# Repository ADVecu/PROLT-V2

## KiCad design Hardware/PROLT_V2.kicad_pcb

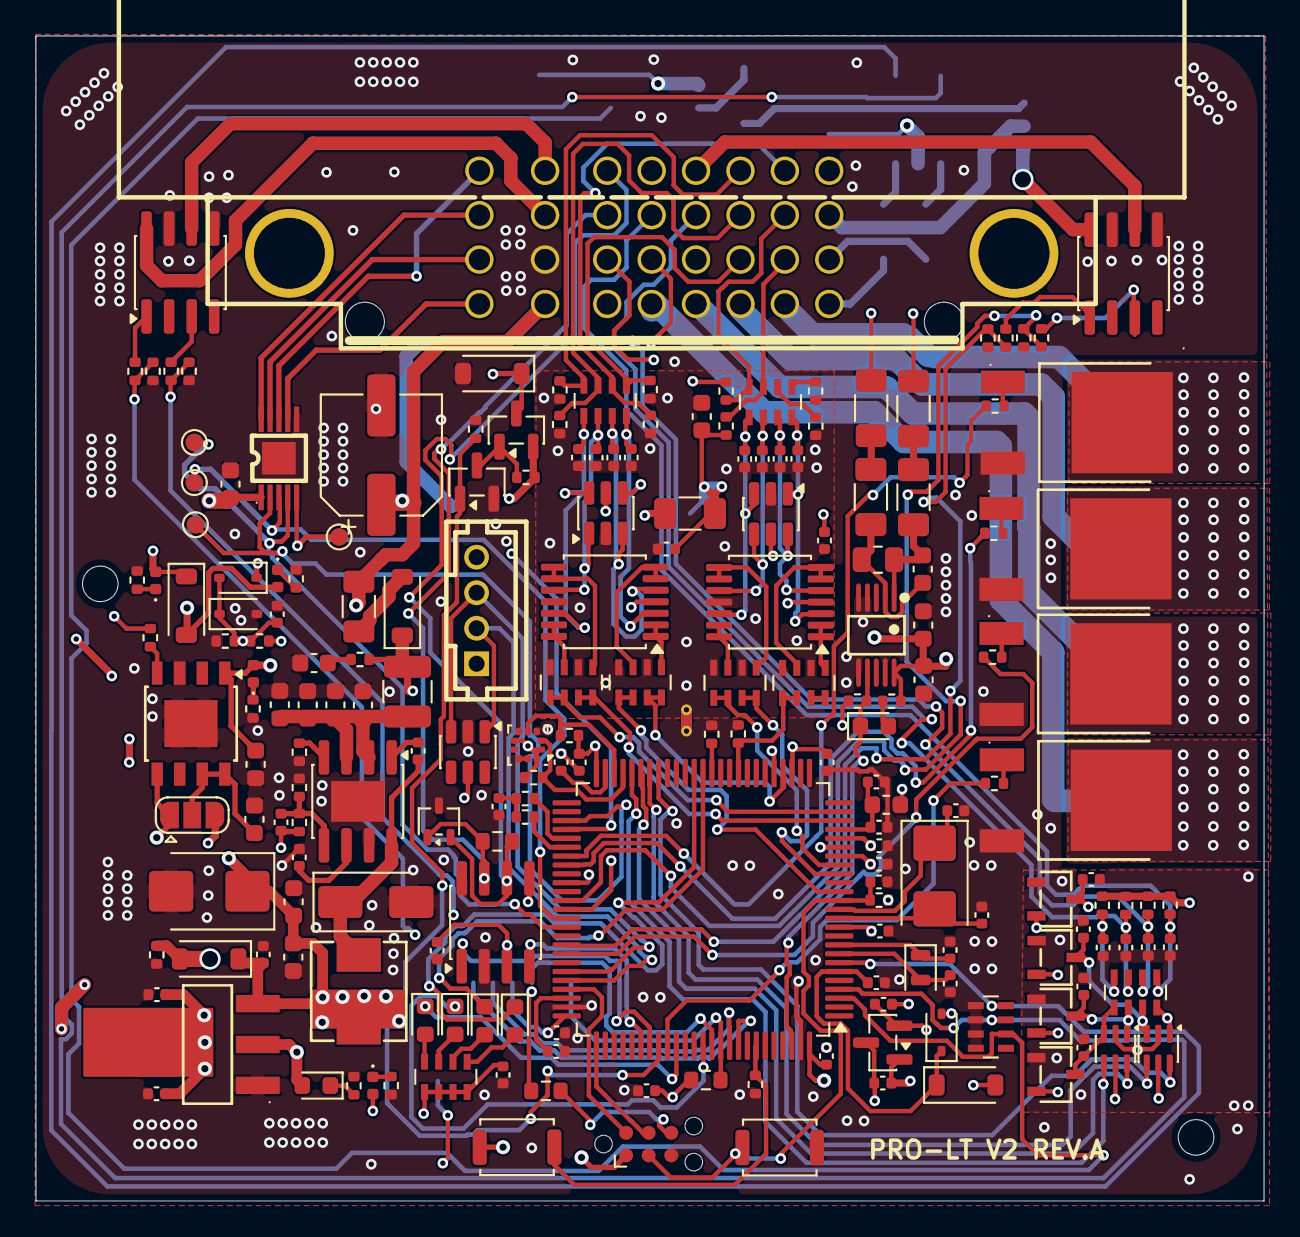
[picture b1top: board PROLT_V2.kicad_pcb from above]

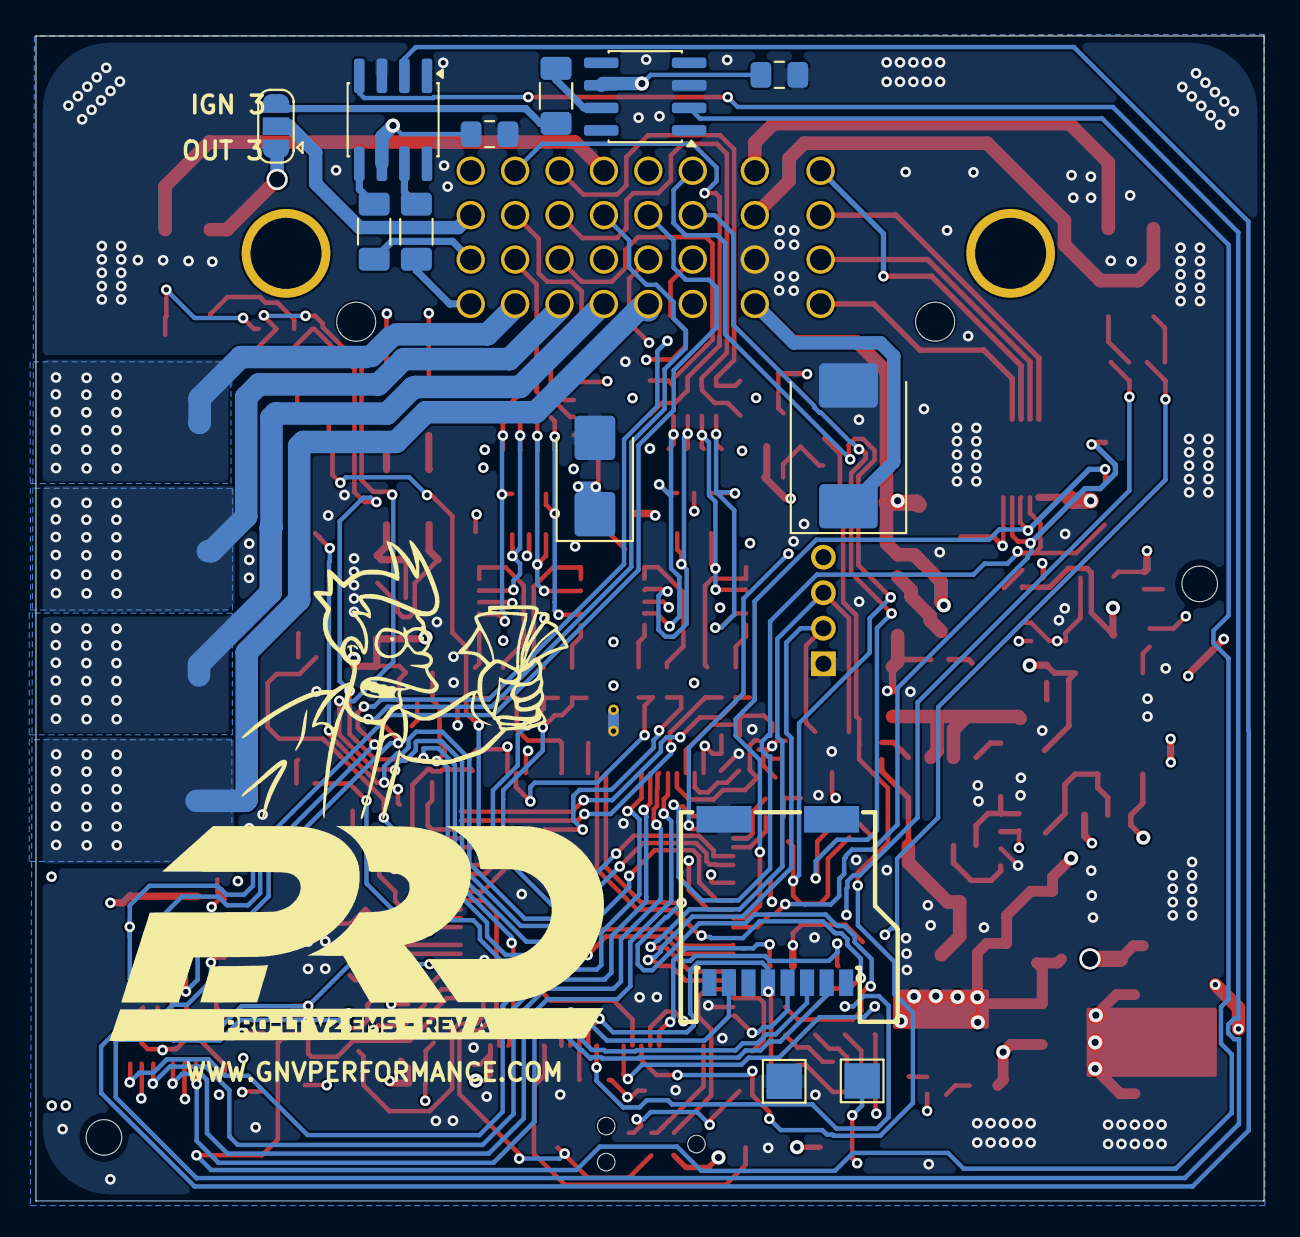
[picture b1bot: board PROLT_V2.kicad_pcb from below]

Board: 4 copper layers, 69.1 x 65.6 mm, 209 parts (13 on the bottom side), 162 nets.

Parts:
C201, C202: 18pF; C_0402_1005Metric
C203: 1uF; C_0402_1005Metric
C204, C208, C209, C210, C211, C212, C213, C214, C221, C223, C224, C226, C309, C312, C410, C411: 100nF; C_0402_1005Metric
C205, C206: 2.2uF; C_0402_1005Metric
C207, C217, C218, C219, C220, C222, C225: 4.7pF; C_0402_1005Metric
C215, C216: 12pF; C_0402_1005Metric
C301: 4.7u; C_0603_1608Metric
C302, C307: 1u; C_0603_1608Metric
C303, C304, C305, C306: 10uF; C_0603_1608Metric
C308, C402, C403, C404, C405, C406, C407, C408, C409: 10nF; C_0402_1005Metric
C310: 220pF; C_0402_1005Metric
C311, C313: 10u; C_0603_1608Metric
C401, C803, C901: 100n; C_0603_1608Metric
C501, C502, C503, C504, C505, C506, C507, C508: 1n; C_0402_1005Metric
C701, C702: 100nF; C_0805_2012Metric_Pad1.18x1.45mm_HandSolder
C801: 1n; C_0603_1608Metric
C802: 22uF; C_0603_1608Metric
C902: 47uF; CP_Elec_6.3x5.4
Card201: TF-004; TF-SMD_TF-004
D201, D202, D303, D307: B5819W; D_SOD-123
D203, D206, D801: GREEN; LED_0603_1608Metric
D204: PESD1CAN; SOT-323_SC-70
D205: RED; LED_0603_1608Metric
D207: BLUE; LED_0603_1608Metric
D208: YELLOW; LED_0603_1608Metric
D301: SM15T33CA; D_SMC
D302, D311, D312: 1N4148WS; D_SOD-323
D304, D305, D308, D310: BLUE; LED_0402_1005Metric
D306: SS34; D_SMA
D309, D401: P6SMB6.8CA; D_SMB
D501, D502, D503, D504: BAT54S,215; SOT-23-3_L3.0-W1.7-P0.95-LS2.9-BR
D601: 1N4148W; D_SOD-123
F301: 500mA; Fuse_1206_3216Metric
F401: SMD1206B035TF; Fuse_1206_3216Metric
FB201: FerriteBead; L_0603_1608Metric
J201: TC2030-NL; Tag-Connect_TC2030-IDC-NL_2x03_P1.27mm_Vertical
JP101: OUT3 SEL; SolderJumper-3_P1.3mm_Open_RoundedPad1.0x1.5mm
JP301: PwSupply; SolderJumper-3_P1.3mm_Open_RoundedPad1.0x1.5mm
L301: 2.2u; L_1210_3225Metric
L302: MWSA0503S-100MT; IND-SMD_L5.4-W5.2
NT401: StarPoint GND; NetTie-2_THT_Pad0.3mm
Q601: AO3407A; SOT-23
Q602: AO3400A; SOT-23
R201, R202: 510; R_0402_1005Metric
R203, R205, R206, R210, R211, R213, R303, R311, R601, R602, R603, R604, R605, R606, R611, R612, R806, R807: 10k; R_0402_1005Metric
R204: 100; R_0603_1608Metric
R207, R208: 2.2k; R_0402_1005Metric
R209: 120; R_0603_1608Metric
R212: 33k; R_0603_1608Metric
R301, R305, R308, R310: 33k; R_0402_1005Metric
R302: 1; R_0402_1005Metric
R304: 23.7k; R_0402_1005Metric
R306: 12k; R_0402_1005Metric
R307: 68k; R_0402_1005Metric
R309: 6.8k; R_0402_1005Metric
R401, R402, R403, R404, R406, R408: 680k; R_0402_1005Metric
R405, R407, R501, R502, R503, R504, R607, R608, R609, R610, R613, R614: 4.7k; R_0402_1005Metric
R701, R702, R703: 100; R_1206_3216Metric_Pad1.30x1.75mm_HandSolder
R801, R802, R803, R804: 4.7k; R_1206_3216Metric_Pad1.30x1.75mm_HandSolder
R805: DNP; R_0805_2012Metric
RN201: R_Pack04; R_Array_Concave_4x0603
RN401, RN402, RN403, RN404, RN405, RN406: 4.7k; R_Array_Concave_4x0603
RN501, RN701: 10k; R_Array_Concave_4x0603
SW201: Boot; SW_Push_SPST_NO_Alps_SKRK
SW202: Reset; SW_Push_SPST_NO_Alps_SKRK
TP301: BATT+; TestPoint_Pad_2.0x2.0mm
TP302: GND; TestPoint_Pad_2.0x2.0mm
TP901: STP1; TestPoint_Pad_D1.0mm
TP902: STP2; TestPoint_Pad_D1.0mm
TP903: STP3; TestPoint_Pad_D1.0mm
TP904: STP4; TestPoint_Pad_D1.0mm
U101: 643340100; CONN-TH_643340100
U201: STM32F407VGTx; LQFP-100_14x14mm_P0.5mm
U202: LPS22HB; ST_HLGA-10_2x2mm_P0.5mm_LayoutBorder3x2y
U203, U401, U402: SRV05-4; SOT-23-6
U204: B4B-PH-K-K; CONN-TH_B4B-PH-K-S-LF-SN
U205: LDL1117S33R; SOT-223-4_L6.5-W3.5-P2.30-LS7.0-BR
U206: TJA1051T-3; SOIC-8_3.9x4.9mm_P1.27mm
U207: REF3033; SOT-23
U301: TLS115; Infineon_PG-DSO-8-43
U302: LMR14020; SOIC-8-1EP_3.9x4.9mm_P1.27mm_EP2.29x3mm
U403, U404: MCP6004T-I-ST; TSSOP-14_4.4x5mm_P0.65mm
U501, U502: 74LVC2G17; SOT-363_SC-70-6
U601, U602, U605, U606: BTS3046SDRATMA1; PG-TO252-3_L6.5-W6.2-P4.57-LS10.0-BR-CW-1
U603, U604: VNLD5160TR-E; SOIC-8_3.9x4.9mm_P1.27mm
U701, U702: MIC4427; SOIC-8_3.9x4.9mm_P1.27mm
U801: MAX9924UAUB+; MSOP-10_L3.0-W3.0-P0.50-LS5.0-BL
U901: DRV8421ADGQR; HVSSOP-10_L3.0-W3.0-P0.50-LS4.9-BL-EP
Y201: 8MHz 20pF; Crystal_SMD_5032-2Pin_5.0x3.2mm
Y202: 32.768 kHz; Crystal_SMD_2012-2Pin_2.0x1.2mm

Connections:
+5V: C217.2, C220.2, C226.2, C310.1, C311.1, C313.1, C701.1, C702.1, C802.1, C803.1, D202.1 (K), D309.1 (K), D310.2 (A), F401.1, JP301.1 (A), L302.2, R307.2, R807.1, U205.3 (VIN), U206.3 (VCC), U207.1 (IN), U301.5 (ADJ), U701.6 (V_{S}), U702.6 (V_{S}), U801.10 (VCC)
/5VA: C401.1, C410.2, C411.2, D401.1 (K), D501.2 (K), D502.2 (K), D503.2 (K), D504.2 (K), F401.2, R405.1, R407.1, R501.1, R502.1, R503.1, R504.1, U401.5 (VP), U402.5 (VP), U403.4 (V+), U404.4 (V+), U501.5 (VCC), U502.5 (VCC)
/5V_SENSOR: C307.1, D305.2 (A), U101.F1, U301.1 (OUT)
/12V_KEY: C901.1, C902.1, D301.1 (A1), D307.2 (A), D308.2 (A), F301.1, R308.2, U101.G1, U901.1 (VM)
/12V_PROT: D303.1 (K), D304.2 (A), D307.1 (K), JP301.3 (B), L301.1, Q601.2 (S), R302.1, R613.1
/A+: U101.H3, U901.10 (OUT1)
/A-: U101.H2, U901.9 (OUT2)
/Analaog/IN5: R401.1, RN401.1 (R1.1)
/Analaog/IN6: R403.1, RN401.2 (R2.1)
/Analaog/OUT1: RN405.7 (R2.2), RN405.8 (R1.2), U201.29 (PA4)
/Analaog/OUT2: RN405.5 (R4.2), RN405.6 (R3.2), U201.15 (PC0)
/Analaog/OUT3: RN406.7 (R2.2), RN406.8 (R1.2), U201.23 (PA0)
/Analaog/OUT4: RN406.5 (R4.2), RN406.6 (R3.2), U201.24 (PA1)
/Analaog/OUT5: RN403.7 (R2.2), RN403.8 (R1.2)
/Analaog/OUT6: R205.2, RN403.5 (R4.2), RN403.6 (R3.2), U201.34 (PC5)
/Analaog/OUT_AT1: RN404.7 (R2.2), RN404.8 (R1.2), U201.17 (PC2)
/Analaog/OUT_AT2: RN404.5 (R4.2), RN404.6 (R3.2), U201.18 (PC3)
/B+: U101.H4, U901.8 (OUT3)
/B-: U101.H1, U901.7 (OUT4)
/CAN_H: D204.1 (A1), R209.1, U101.F3, U206.7 (CANH)
/CAN_L: D204.2 (A2), R209.2, U101.F4, U206.6 (CANL)
/Digital/HALL_IN_4: C502.1, R502.2, RN501.4 (R4.1)
/Digital/HALL_OUT_1: U201.43 (PE12), U501.6
/Digital/HALL_OUT_2: U201.44 (PE13), U501.4
/Digital/HALL_OUT_3: U201.45 (PE14), U502.6
/Digital/HALL_OUT_4: U201.46 (PE15), U502.4
/IGN1_OUT: R701.2, U101.A1
/IGN2_OUT: R702.2, U101.A2
/IGN3_OUT: JP101.3 (B), R703.2
/INJ1_OUT: U101.E1, U601.2 (DRAIN)
/INJ2_OUT: U101.D1, U602.2 (DRAIN)
/INJ3_OUT: U101.C1, U605.2 (DRAIN)
/INJ4_OUT: U101.B1, U606.2 (DRAIN)
/IN_AUX1: R406.1, RN402.3 (R3.1), U101.C3
/IN_AUX2: R408.1, RN402.4 (R4.1), U101.C4
/IN_CLT: R407.2, RN401.4 (R4.1), U101.B3
/IN_CMP: C503.1, R503.2, RN501.1 (R1.1), U101.E3
/IN_D1: C504.1, R504.2, RN501.2 (R2.1), U101.D2
/IN_D2: C501.1, R501.2, RN501.3 (R3.1), U101.D3
/IN_IAT: R405.2, RN401.3 (R3.1), U101.B2
/IN_MAP: R404.1, RN402.2 (R2.1), U101.B4
/IN_TPS: R402.1, RN402.1 (R1.1), U101.C2
/Ignition/IN_IGN1: RN701.8 (R1.2), U201.7 (PC13), U701.2 (INA)
/Ignition/IN_IGN2: RN701.7 (R2.2), U201.4 (PE5), U701.4 (INB)
/Ignition/IN_IGN3: RN701.6 (R3.2), U201.3 (PE4), U702.2 (INA)
/MCU/BOOT: R211.1, SW201.2, U201.94 (BOOT0)
/MCU/I2C_SCL: R208.2, U201.47 (PB10), U202.2 (SCL)
/MCU/I2C_SDA: R207.2, U201.48 (PB11), U202.4 (SDA)
/MCU/IN_AUX2_(PC4/PE9): U201.33 (PC4), U201.40 (PE9)
/MCU/IN_VIGN_(PA5): C312.2, D311.2 (A), D312.1 (K), R308.1, R309.2, U201.30 (PA5)
/MCU/LED1: D205.1 (K), U201.85 (PD4)
/MCU/LED2: D206.1 (K), U201.88 (PD7)
/MCU/LED3: D207.1 (K), U201.38 (PE7)
/MCU/LED4: D208.1 (K), U201.39 (PE8)
/MCU/OUT_INJ1_(PD3): R601.1, U201.84 (PD3)
/MCU/OUT_INJ2_(PA9): R602.1, U201.68 (PA9)
/MCU/OUT_INJ3_(PD11): R611.1, U201.58 (PD11)
/MCU/OUT_INJ4_(PD10): R612.1, U201.57 (PD10)
/MCU/OUT_INJ5_(PD2): Q602.1 (G), R614.1, U201.83 (PD2)
/MCU/OUT_INJ6_(PA8): R604.2, R609.2, U201.67 (PA8)
/MCU/OUT_INJ7_(PD15): R606.2, R610.2, U201.62 (PD15)
/MCU/OUT_PWM1_(PD13): R603.2, R607.2, U201.60 (PD13)
/MCU/OUT_PWM2_(PC6): R605.2, R608.2, U201.63 (PC6)
/MCU/RESET: C223.2, J201.3 (~RESET), R213.2, SW202.2, U201.14 (NRST)
/MCU/RXDCAN: U201.81 (PD0), U206.4 (RXD)
/MCU/SD_CS: Card201.2 (CD/DAT3), U201.92 (PB6)
/MCU/SD_MISO: Card201.7 (DAT0), R212.1, U201.90 (PB4)
/MCU/SD_MOSI: Card201.3 (CMD), U201.91 (PB5)
/MCU/SD_SCK: Card201.5 (CLK), R204.1, U201.89 (PB3)
/MCU/SWCLK: J201.4 (SWCLK), U201.76 (PA14)
/MCU/SWDIO: J201.2 (SWDIO), U201.72 (PA13)
/MCU/SWO: J201.6 (SWO), R204.2
/MCU/TXDCAN: U201.82 (PD1), U206.1 (TXD)
/MCU/UART8_TX_(PE1): D801.1 (K), R806.2, U201.98 (PE1), U801.7 (COUT)
/MCU/USBD+: U201.71 (PA12), U203.1 (IO1), U204.2
/MCU/USBD-: U201.70 (PA11), U203.3 (IO2), U204.3
/MCU/VBAT: C207.2, D201.1 (K), D302.1 (K), U201.6 (VBAT)
/MCU/VBUS: D202.2 (A), R206.1, U203.5 (VP), U204.4
/MCU/VDDA: C214.2, C225.2, FB201.2, U201.22 (VDDA)
/MCU/VREF: C204.2, C222.2, U201.21 (VREF+), U207.2 (OUT)
/OUT_1: U101.G3, U603.8 (D1)
/OUT_2: U101.G4, U603.6 (D2)
/OUT_3: JP101.1 (A), U604.8 (D1)
/OUT_4: U101.D4, U604.6 (D2)
/Power/5V_SENSOR_PG: R303.1, U301.4 (PG)
/Power/SensorTrackerPS: C302.1, JP301.2 (C), U301.7 (EN), U301.8 (IN)
/STEPPER_IN1: TP901.1 (1_1), U201.53 (PB14), U901.2 (IN1)
/STEPPER_IN2: TP902.1 (1_1), U201.64 (PC7), U901.3 (IN2)
/STEPPER_IN3: TP903.1 (1_1), U201.65 (PC8), U901.4 (IN3)
/STEPPER_IN4: TP904.1 (1_1), U201.54 (PB15), U901.5 (IN4)
/TACH: D601.1 (K), Q601.3 (D), U101.A4
/V33: C208.1, C209.1, C210.1, C211.1, C212.1, C213.1, C218.2, C219.2, C221.2, C224.2, Card201.4 (VDD), D201.2 (A), D203.2 (A), D311.1 (K), FB201.1, J201.1 (VCC), R207.1, R208.1, R212.2, R213.1, R303.2, R806.1, RN201.1 (R1.1), RN201.2 (R2.1), RN201.3 (R3.1), RN201.4 (R4.1), SW201.1, U201.11 (VDD), U201.19 (VDD), U201.28 (VDD), U201.50 (VDD), U201.75 (VDD), U201.100 (VDD), U202.1 (Vdd_IO), U202.6 (~CS), U202.10 (VDD), U205.2 (VOUT), U205.4 (VOUT), U206.5 (VIO)
/VR+: R801.1, U101.F2
/VR-: R802.1, U101.E2
GND: C201.1, C202.1, C203.2, C204.1, C205.1, C206.1, C207.1, C208.2, C209.2, C210.2, C211.2, C212.2, C213.2, C214.1, C215.1, C216.1, C217.1, C218.1, C219.1, C221.1, C223.1, C224.1, C225.1, C226.1, C301.2, C302.2, C303.2, C304.2, C305.2, C306.2, C307.2, C308.2, C311.2, C312.1, C313.2, C701.2, C702.2, C802.2, C803.2, C901.2, C902.2, Card201.6 (VSS), Card201.9 (GND), Card201.10 (GND), D204.3 (Com), D301.2 (A2), D306.2 (A), D309.2 (A), D312.2 (A), D401.2 (A), D601.2 (A), J201.5 (GND), NT401.2, Q602.2 (S), R203.2, R205.1, R206.2, R210.2, R211.2, R301.1, R304.2, R305.1, R306.2, R309.1, R310.1, R311.2, R603.1, R604.1, R605.1, R606.1, R614.2, RN701.1 (R1.1), RN701.2 (R2.1), RN701.3 (R3.1), RN701.4 (R4.1), SW202.1, TP302.1 (1_1), U101.G2, U201.10 (VSS), U201.27 (VSS), U201.74 (VSS), U201.99 (VSS), U202.3 (GND), U202.5 (SA0), U202.8 (GND), U202.9 (GND), U203.2 (VN), U204.1, U205.1 (GND), U206.2 (GND), U206.8 (S), U301.3 (GND), U301.9 (GND), U302.7 (GND), U302.9 (GND), U601.3 (SOURCE), U602.3 (SOURCE), U603.5 (S2), U603.7 (S1), U604.5 (S2), U604.7 (S1), U605.3 (SOURCE), U606.3 (SOURCE), U701.3 (GND), U702.3 (GND), U801.4 (BIAS), U801.5 (GND), U801.6 (ZERO_EN), U801.9 (INT_THRS), U901.6 (GND), U901.11 (GND)
GNDA: C220.1, C222.1, C401.2, C402.2, C403.2, C404.2, C405.2, C406.2, C407.2, C408.2, C409.2, C410.1, C411.1, C501.2, C502.2, C503.2, C504.2, C505.2, C506.2, C507.2, C508.2, D501.1 (A), D502.1 (A), D503.1 (A), D504.1 (A), NT401.1, R401.2, R402.2, R403.2, R404.2, R406.2, R408.2, RN403.2 (R2.1), RN403.4 (R4.1), RN404.2 (R2.1), RN404.4 (R4.1), RN405.2 (R2.1), RN405.4 (R4.1), RN406.2 (R2.1), RN406.4 (R4.1), U101.E4, U201.20 (VSSA), U207.3 (GND), U401.2 (VN), U402.2 (VN), U403.11 (V-), U404.11 (V-), U501.2 (GND), U502.2 (GND)
unnamed: C203.1, R201.1, R202.1
unnamed: C301.1, R302.2
unnamed: D203.1 (K), R210.1
unnamed: D205.2 (A), RN201.8 (R1.2)
unnamed: D206.2 (A), RN201.7 (R2.2)
unnamed: D207.2 (A), RN201.6 (R3.2)
unnamed: D208.2 (A), RN201.5 (R4.2)
unnamed: D302.2 (A), TP301.1 (1_1)
unnamed: D303.2 (A), F301.2
unnamed: D304.1 (K), R301.2
unnamed: D305.1 (K), R305.2
unnamed: C309.1, D306.1 (K), L302.1, U302.8 (SW)
unnamed: D308.1 (K), R310.2
unnamed: D310.1 (K), R311.1
unnamed: C506.1, D501.3 (AK), RN501.5 (R4.2), U502.3
unnamed: C505.1, D502.3 (AK), RN501.6 (R3.2), U502.1
unnamed: C508.1, D503.3 (AK), RN501.7 (R2.2), U501.3
unnamed: C507.1, D504.3 (AK), RN501.8 (R1.2), U501.1
unnamed: D801.2 (A), R807.2
unnamed: JP101.2 (C), U101.A3
unnamed: Q601.1 (G), Q602.3 (D), R613.2
unnamed: R801.2, R803.1
unnamed: R802.2, R804.1
unnamed: C402.1, RN401.8 (R1.2), U401.1 (IO1), U403.3 (+)
unnamed: C404.1, RN401.7 (R2.2), U401.6 (IO4), U403.5 (+)
unnamed: C406.1, RN401.6 (R3.2), U401.4 (IO3), U403.10 (+)
unnamed: C408.1, RN401.5 (R4.2), U401.3 (IO2), U403.12 (+)
unnamed: C403.1, RN402.8 (R1.2), U402.4 (IO3), U404.3 (+)
unnamed: C405.1, RN402.7 (R2.2), U402.3 (IO2), U404.5 (+)
unnamed: C407.1, RN402.6 (R3.2), U402.1 (IO1), U404.10 (+)
unnamed: C409.1, RN402.5 (R4.2), U402.6 (IO4), U404.12 (+)
unnamed: RN403.1 (R1.1), U403.1, U403.2 (-)
unnamed: RN403.3 (R3.1), U403.6 (-), U403.7
unnamed: RN404.1 (R1.1), U403.8, U403.9 (-)
unnamed: RN404.3 (R3.1), U403.13 (-), U403.14
unnamed: RN405.1 (R1.1), U404.1, U404.2 (-)
unnamed: RN405.3 (R3.1), U404.6 (-), U404.7
unnamed: RN406.1 (R1.1), U404.8, U404.9 (-)
unnamed: RN406.3 (R3.1), U404.13 (-), U404.14
unnamed: R203.1, U201.37 (PB2)
unnamed: C215.2, U201.8 (PC14), Y202.2
unnamed: C216.2, U201.9 (PC15), Y202.1
unnamed: R201.2, U201.55 (PD8)
unnamed: R202.2, U201.56 (PD9)
unnamed: C201.2, U201.12 (PH0), Y201.2
unnamed: C202.2, U201.13 (PH1), Y201.1
unnamed: C205.2, U201.49 (VCAP_1)
unnamed: C206.2, U201.73 (VCAP_2)
unnamed: C309.2, U302.1 (BOOT)
unnamed: C303.1, C304.1, C305.1, C306.1, L301.2, U302.2 (VIN), U302.3 (EN)
unnamed: C310.2, R306.1, R307.1, U302.5 (FB)
unnamed: R304.1, U302.4 (RT)
unnamed: C308.1, U302.6 (SS)
unnamed: R601.2, U601.1 (IN)
unnamed: R602.2, U602.1 (IN)
unnamed: R607.1, U603.1 (IN1)
unnamed: R608.1, U603.3 (IN2)
unnamed: R609.1, U604.1 (IN1)
unnamed: R610.1, U604.3 (IN2)
unnamed: R611.2, U605.1 (IN)
unnamed: R612.2, U606.1 (IN)
unnamed: R701.1, U701.7 (OUTA)
unnamed: R702.1, U701.5 (OUTB)
unnamed: R703.1, U702.7 (OUTA)
unnamed: C801.1, R803.2, R805.2, U801.1 (IN+)
unnamed: C801.2, R804.2, R805.1, U801.2 (IN-)

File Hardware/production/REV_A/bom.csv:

Designator,Footprint,Quantity,Value,LCSC Part #
"C201, C202",0402,2,18pF,C1549
C203,0402,1,1uF,C29266
"C204, C208, C209, C210, C211, C212, C213, C214, C221, C223, C224, C226, C309, C312, C410, C411, C902, C903, C904",0402,19,100nF,C1525
"C205, C206",0402,2,2.2uF,C12530
"C207, C217, C218, C219, C220, C222, C225, C906",0402,8,4.7pF,C23733
"C215, C216",0402,2,12pF,C1547
C301,0603,1,4.7u,C19666
"C302, C307",0603,2,1u,C15849
"C303, C304, C305, C306",0603,4,10uF,C96446
"C308, C402, C403, C404, C405, C406, C407, C408, C409, C905",0402,10,10nF,C15195
C310,0402,1,220pF,C1530
"C311, C313",0603,2,10u,C92487
"C401, C803",0603,2,100n,C14663
"C501, C502, C503, C504, C505, C506, C507, C508",0402,8,1n,C1523
"C701, C702",0805,2,100nF,C519980
C801,0603,1,1n,C1588
C802,0603,1,22uF,C59461
C901,1206,1,10uF,C7432781
CARD201,TF-SMD_TF-004,1,TF-004,C428454
"D201, D202",D_SOD-123,2,B5819W,
"D203, D206, D801",0603,3,GREEN,C965804
D204,SOT-323_SC-70,1,PESD1CAN,C152727
D205,0603,1,RED,C2286
D207,0603,1,BLUE,C497940
D208,0603,1,YELLOW,C72038
D301,D_SMC,1,SM15T33CA,C151281
"D302, D311, D312",D_SOD-323,3,1N4148WS,C2128
"D303, D307",D_SOD-123,2,B5819W,C8598
"D304, D305, D308, D310",0402,4,BLUE,C434447
D306,D_SMA,1,SS34,C8678
"D309, D401",D_SMB,2,P6SMB6.8CA,C78395
"D501, D502, D503, D504",SOT-23-3_L3.0-W1.7-P0.95-LS2.9-BR,4,"BAT54S,215",C47546
D601,D_SOD-123,1,1N4148W,C917030
F301,1206,1,500mA,C976305
F401,1206,1,SMD1206B035TF,C269114
FB201,0603,1,FerriteBead,C19330
L301,1210,1,2.2u,C250227
L302,IND-SMD_L5.4-W5.2,1,MWSA0503S-100MT,C408412
Q601,SOT-23,1,AO3407A,C15155
Q602,SOT-23,1,AO3400A,C20917
"R201, R202",0402,2,510,C25170
"R203, R206, R210, R211, R213, R303, R311, R601, R602, R603, R604, R605, R606, R611, R612, R806, R807",0402,17,10k,C60490
"R207, R208",0402,2,2.2k,C163447
R209,0603,1,120,C22787
R212,0603,1,33k,C4216
"R301, R305, R308, R310",0402,4,33k,C25779
R302,0402,1,1,C25086
R304,0402,1,23.7k,C327362
R306,0402,1,12k,C25752
R307,0402,1,68k,C36871
R309,0402,1,6.8k,C25917
"R401, R402, R403, R404, R406, R408",0402,6,680k,C163456
"R405, R407, R501, R502, R503, R504, R607, R608, R609, R610, R613, R614",0402,12,4.7k,C25900
"R701, R702, R703",1206,3,100,C17901
"R801, R802, R803, R804",1206,4,10k,C17928
R901,0402,1,1M,C2906900
"R902, R903",1206,2,0.22,C49164951
RN201,R_Array_Concave_4x0603,1,R_Pack04,C25510
"RN401, RN402, RN403, RN404, RN405, RN406",R_Array_Concave_4x0603,6,4.7k,C66697
"RN501, RN701",R_Array_Concave_4x0603,2,10k,C29718
U101,CONN-TH_643340100,1,643340100,C293657
U201,LQFP-100_14x14mm_P0.5mm,1,STM32F407VGTx,C12345
U202,ST_HLGA-10_2x2mm_P0.5mm_LayoutBorder3x2y,1,LPS22HB,
U203,SOT-23-6,1,SRV05-4,
U204,CONN-TH_B4B-PH-K-S-LF-SN,1,B4B-PH-K-K,C5305780
U205,SOT-223-4_L6.5-W3.5-P2.30-LS7.0-BR,1,LDL1117S33R,C435835
U206,SOIC-8_3.9x4.9mm_P1.27mm,1,TJA1051T-3,C38695
U207,SOT-23,1,REF3033,C36658
U301,Infineon_PG-DSO-8-43,1,TLS115,C3747428
U302,SOIC-8-1EP_3.9x4.9mm_P1.27mm_EP2.29x3mm,1,LMR14020,C187824
"U401, U402",SOT-23-6,2,SRV05-4,C2836319
"U403, U404",TSSOP-14_4.4x5mm_P0.65mm,2,MCP6004T-I-ST,C50282
"U501, U502",SOT-363_SC-70-6,2,74LVC2G17,C80500
"U601, U602, U605, U606",PG-TO252-3_L6.5-W6.2-P4.57-LS10.0-BR-CW-1,4,BTS3046SDRATMA1,C2680440
"U603, U604",SOIC-8_3.9x4.9mm_P1.27mm,2,VNLD5160TR-E,C377942
"U701, U702",SOIC-8_3.9x4.9mm_P1.27mm,2,MIC4427,C144205
U801,MSOP-10_L3.0-W3.0-P0.50-LS5.0-BL,1,MAX9924UAUB+,C143633
U901,RES-ADJ-SMD_3P-L3.8-W3.0-P2.00-BL-FS,1,10k,C911365
U902,HTSSOP-28_L9.7-W4.4-P0.65-LS6.4-BL-EP,1,DRV8825PWPR,C81582
Y201,Crystal_SMD_5032-2Pin_5.0x3.2mm,1,8MHz 20pF,C112566
Y202,Crystal_SMD_2012-2Pin_2.0x1.2mm,1,32.768 kHz,C99009

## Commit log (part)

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2026-06-29 Repo Init
